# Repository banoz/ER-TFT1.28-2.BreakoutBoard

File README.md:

# ER-TFT1.28-2.BreakoutBoard
1.28" round TFT display with capacitive touchscreen breakout board based on ESP32-S3-BOX schematics.

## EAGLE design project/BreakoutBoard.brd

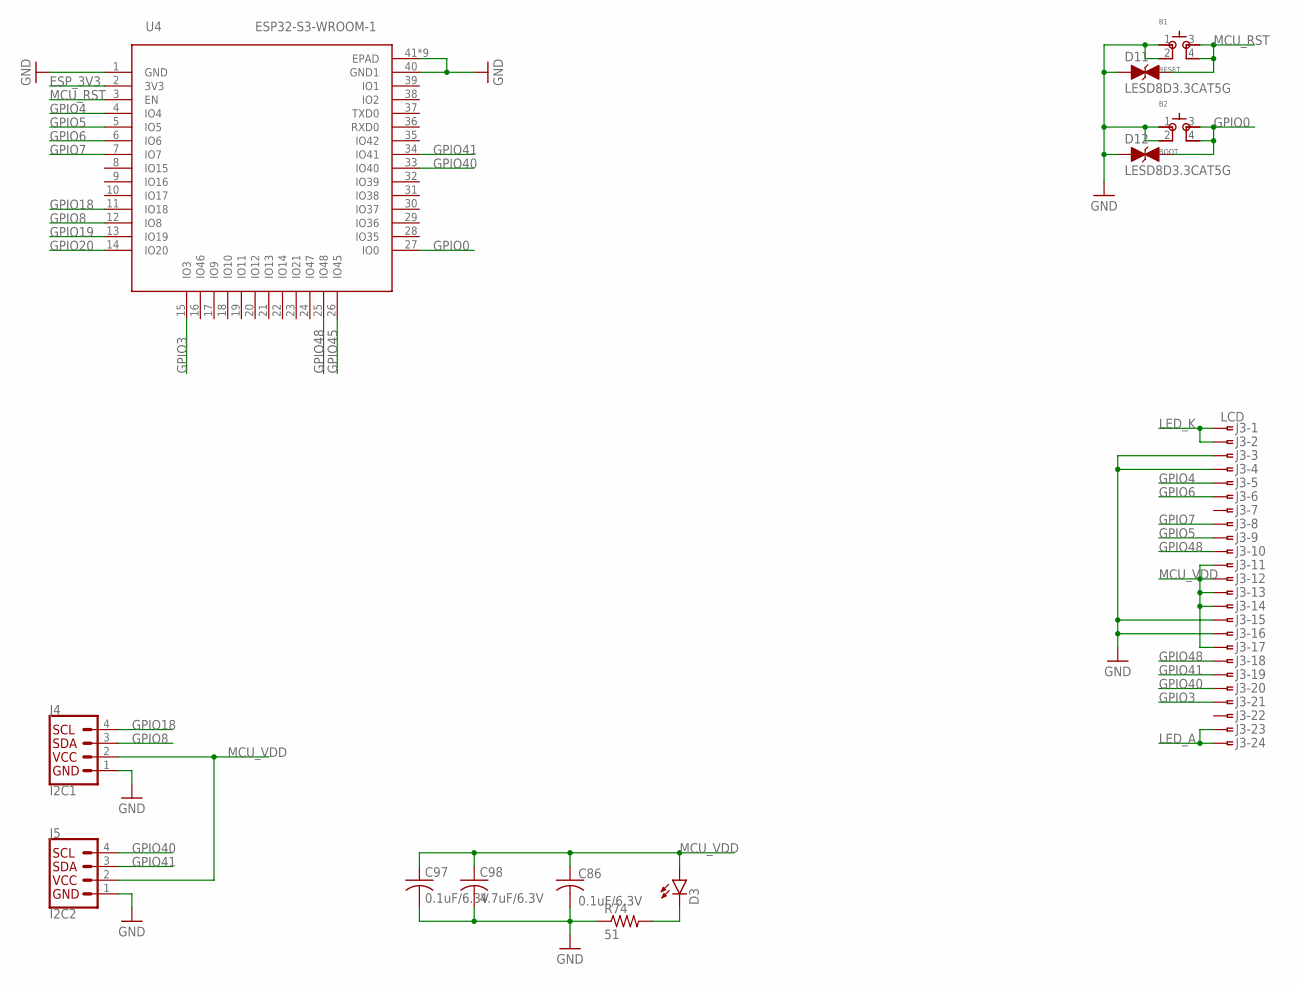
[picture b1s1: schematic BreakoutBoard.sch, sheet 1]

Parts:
B1: RESET; SKSCLDE010; LCSC C115362
B2: BOOT; SKSCLDE010; LCSC C115362
C86, C97: 0.1uF/6.3V; C0402; LCSC C541406
C98: 4.7uF/6.3V; C0402; LCSC C106859
D3: LEDCHIPLED_1206; CHIPLED_1206; LCSC C375534
D11, D12: LESD8D3.3CAT5G; SOD882; LCSC C172409
J3: LCD; OK-24F024-04
J4: I2C1; JST04_1MM_VERT; LCSC C495539
J5: I2C2; JST04_1MM_VERT; LCSC C495539
R74: 51; R0201; LCSC C163499
U4: ESP32-S3-WROOM-1; QFN60_ESP32-S3-WROOM-1_EXP

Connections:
ESP_3V3: U4.2 (3V3); also elsewhere on the board
GND: B1.1, B1.2, B2.1, B2.2, C86.2, C97.2, C98.2, D11.A, D12.A, J3.3, J3.4, J3.15, J3.16, J4.1, J5.1, R74.1, U4.1 (GND), U4.40 (GND1), U4.41 (EPAD), U4.42 (EPAD), U4.43 (EPAD), U4.44 (EPAD), U4.45 (EPAD), U4.46 (EPAD), U4.47 (EPAD), U4.48 (EPAD), U4.49 (EPAD); also elsewhere on the board
GPIO0: B2.3 (4), B2.4 (3), D12.C, U4.27 (IO0)
GPIO3: J3.21, U4.15 (IO3)
GPIO4: J3.5, U4.4 (IO4)
GPIO5: J3.9, U4.5 (IO5)
GPIO6: J3.6, U4.6 (IO6)
GPIO7: J3.8, U4.7 (IO7)
GPIO8: J4.3, U4.12 (IO8)
GPIO18: J4.4, U4.11 (IO18)
GPIO19: U4.13 (IO19); also elsewhere on the board
GPIO20: U4.14 (IO20); also elsewhere on the board
GPIO40: J3.20, J5.4, U4.33 (IO40)
GPIO41: J3.19, J5.3, U4.34 (IO41)
GPIO45: U4.26 (IO45); also elsewhere on the board
GPIO48: J3.10, J3.18, U4.25 (IO48); also elsewhere on the board
LED_A: J3.23, J3.24; also elsewhere on the board
LED_K: J3.1, J3.2; also elsewhere on the board
MCU_RST: B1.3 (4), B1.4 (3), D11.C, U4.3 (EN); also elsewhere on the board
MCU_VDD: C86.1, C97.1, C98.1, D3.A, J3.11, J3.12, J3.13, J3.14, J3.17, J4.2, J5.2; also elsewhere on the board
unnamed: D3.C, R74.2

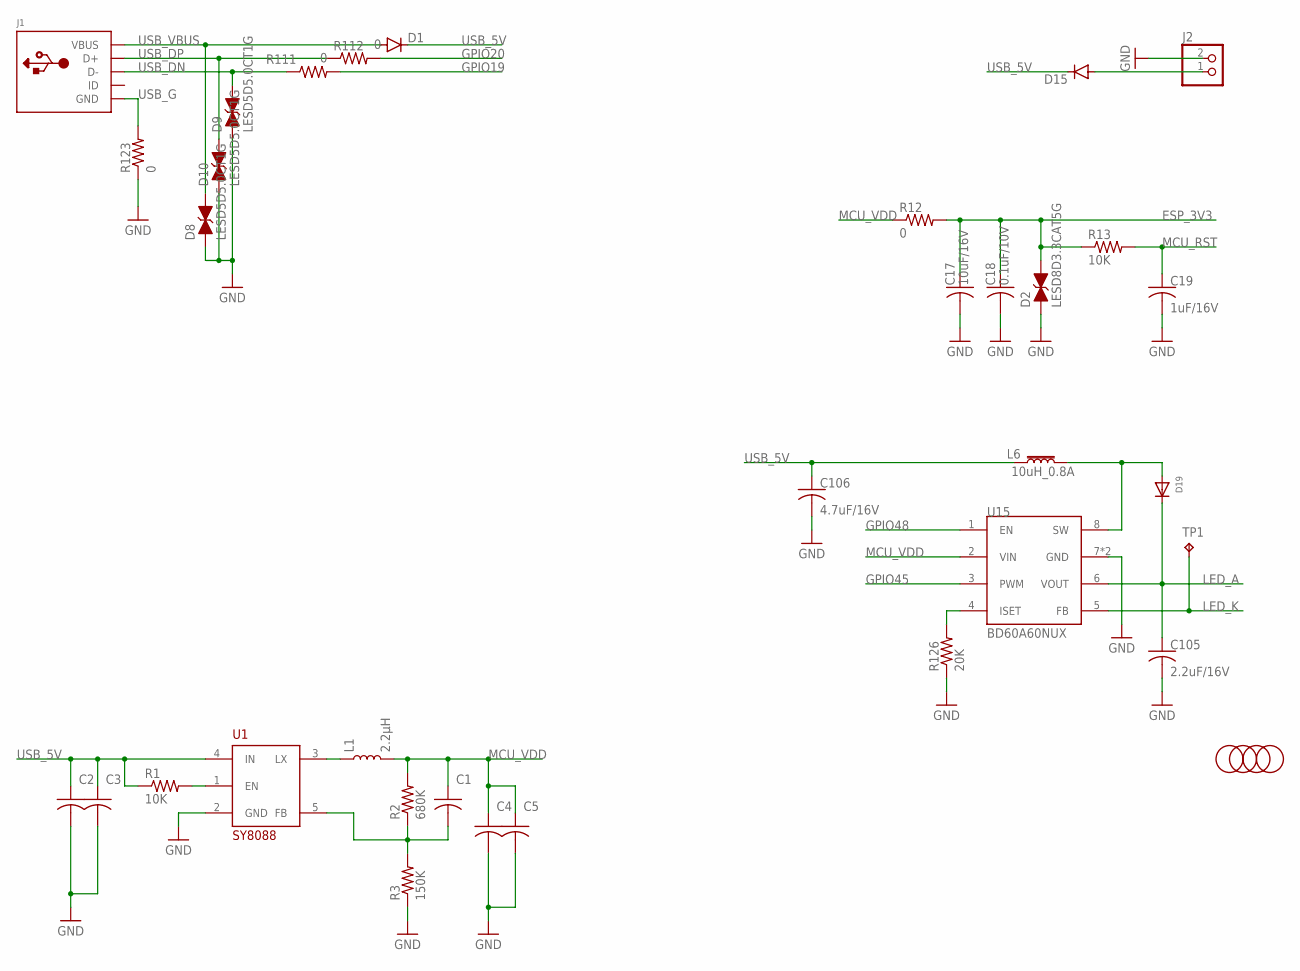
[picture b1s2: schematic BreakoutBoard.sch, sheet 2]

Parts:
C1: 22pF/50V; C0402; LCSC C106203
C2, C17: 10uF/16V; C0603; LCSC C86275
C3: 0.1uF/10V; C0603; LCSC C161163
C4, C18: 0.1uF/10V; C0402; LCSC C161163
C5: 10uF/16V; C0402; LCSC C86275
C19: 1uF/16V; C0402; LCSC C77007
C105: 2.2uF/16V; C0603; LCSC C106853
C106: 4.7uF/16V; C0603; LCSC C277476
D1, D15: DIODE-SOD123; SOD123; LCSC C511872
D2: LESD8D3.3CAT5G; SOD882; LCSC C172409
D8, D9, D10: LESD5D5.0CT1G; SOD523; LCSC C383211
D19: DIODESOD-523; SOD-523; LCSC C253516
J1: MICROBUILDER_USBMICRO_20329; MICROBUILDER_4UCONN_20329; LCSC C40946
J2: JST_2PIN-SMT; JST-PH-2-SMT; LCSC C64658
L1: 2.2μH; INDUCTOR_4X4MM; LCSC C370436
L6: 10uH_0.8A; L3012S; LCSC C518881
R1, R13: 10K; R0402; LCSC C60490
R2: 680K; R0402; LCSC C163456
R3: 150K; R0402; LCSC C93947
R12, R123: 0; R0603; LCSC C100044
R111, R112: 0; R0201; LCSC C106227
R126: 20K; R0402; LCSC C326980
TP1: TPTP06R; TP06R
U1: SY8088; SOT23-5; LCSC C79313
U15: BD60A60NUX; VSON008X2030; LCSC C2678724
U$1, U$2, U$4, U$5: FIDUCIAL; FIDUCIAL_1MM

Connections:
ESP_3V3: C17.1, C18.1, D2.C, R12.2, R13.1; also elsewhere on the board
GND: C2.2, C3.2, C4.2, C5.2, C17.2, C18.2, C19.2, C105.2, C106.2, D2.A, D8.A, D9.A, D10.A, J2.2 (1), R3.1, R123.1, R126.1, U1.2 (GND), U15.7 (GND), U15.PAD (GND); also elsewhere on the board
GPIO19: R111.2; also elsewhere on the board
GPIO20: R112.2; also elsewhere on the board
GPIO45: U15.3 (PWM); also elsewhere on the board
GPIO48: U15.1 (EN); also elsewhere on the board
LED_A: C105.1, D19.K (C), U15.6 (VOUT); also elsewhere on the board
LED_K: TP1.TP, U15.5 (FB); also elsewhere on the board
MCU_RST: C19.1, R13.2; also elsewhere on the board
MCU_VDD: C1.1, C4.1, C5.1, L1.P$2 (2), R2.2, R12.1, U15.2 (VIN); also elsewhere on the board
unnamed: D19.A, L6.P$2 (2), U15.8 (SW)
unnamed: D15.A, J2.1 (2)
unnamed: R1.2, U1.1 (EN)
unnamed: L1.P$1 (1), U1.3 (LX)
unnamed: C1.2, R2.1, R3.2, U1.5 (FB)
unnamed: R126.2, U15.4 (ISET)
USB_5V: C2.1, C3.1, C106.1, D1.C, D15.C, L6.P$1 (1), R1.1, U1.4 (IN)
USB_DN: D9.C, J1.D-, R111.1
USB_DP: D10.C, J1.D+, R112.1
USB_G: J1.BASE@1 (GND), J1.BASE@2 (GND), J1.GND, J1.SPRT@1 (GND), J1.SPRT@2 (GND), J1.SPRT@3 (GND), J1.SPRT@4 (GND), R123.2
USB_VBUS: D1.A, D8.C, J1.VBUS

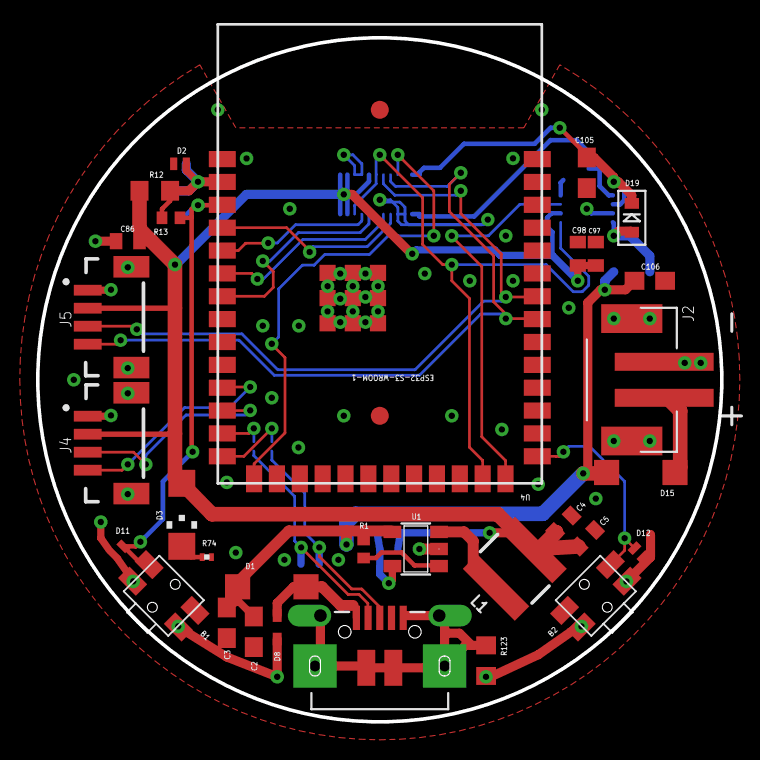
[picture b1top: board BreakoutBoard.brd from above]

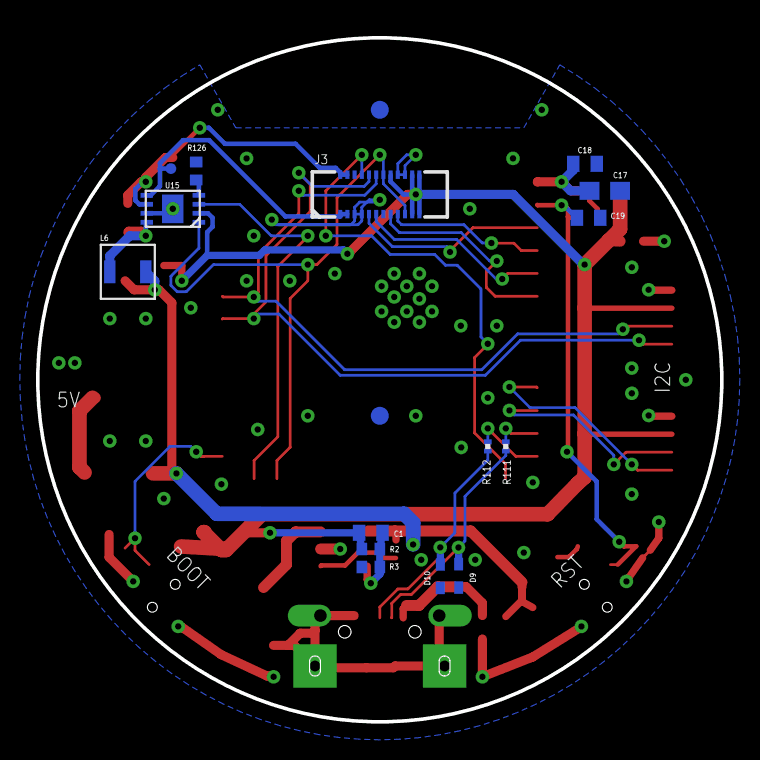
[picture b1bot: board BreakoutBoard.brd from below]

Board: 2 copper layers, 38.0 x 38.0 mm, 50 parts (17 on the bottom side), 32 nets.

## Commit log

2021-11-14 Create LICENSE
2021-11-14 Initial state
2021-12-09 Layout complete
2022-05-15 Layout optimization
2022-06-18 Display pinout fix

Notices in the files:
parts and their libraries:
SparkFun-Connectors: Licensing: Creative Commons ShareAlike 4.0 International - https://creativecommons.org/licenses/by-sa/4.0
